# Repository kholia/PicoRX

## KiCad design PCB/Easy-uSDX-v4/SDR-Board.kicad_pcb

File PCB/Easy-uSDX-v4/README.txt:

https://www.w0qe.com/Projects/rf_clipper_2016.html

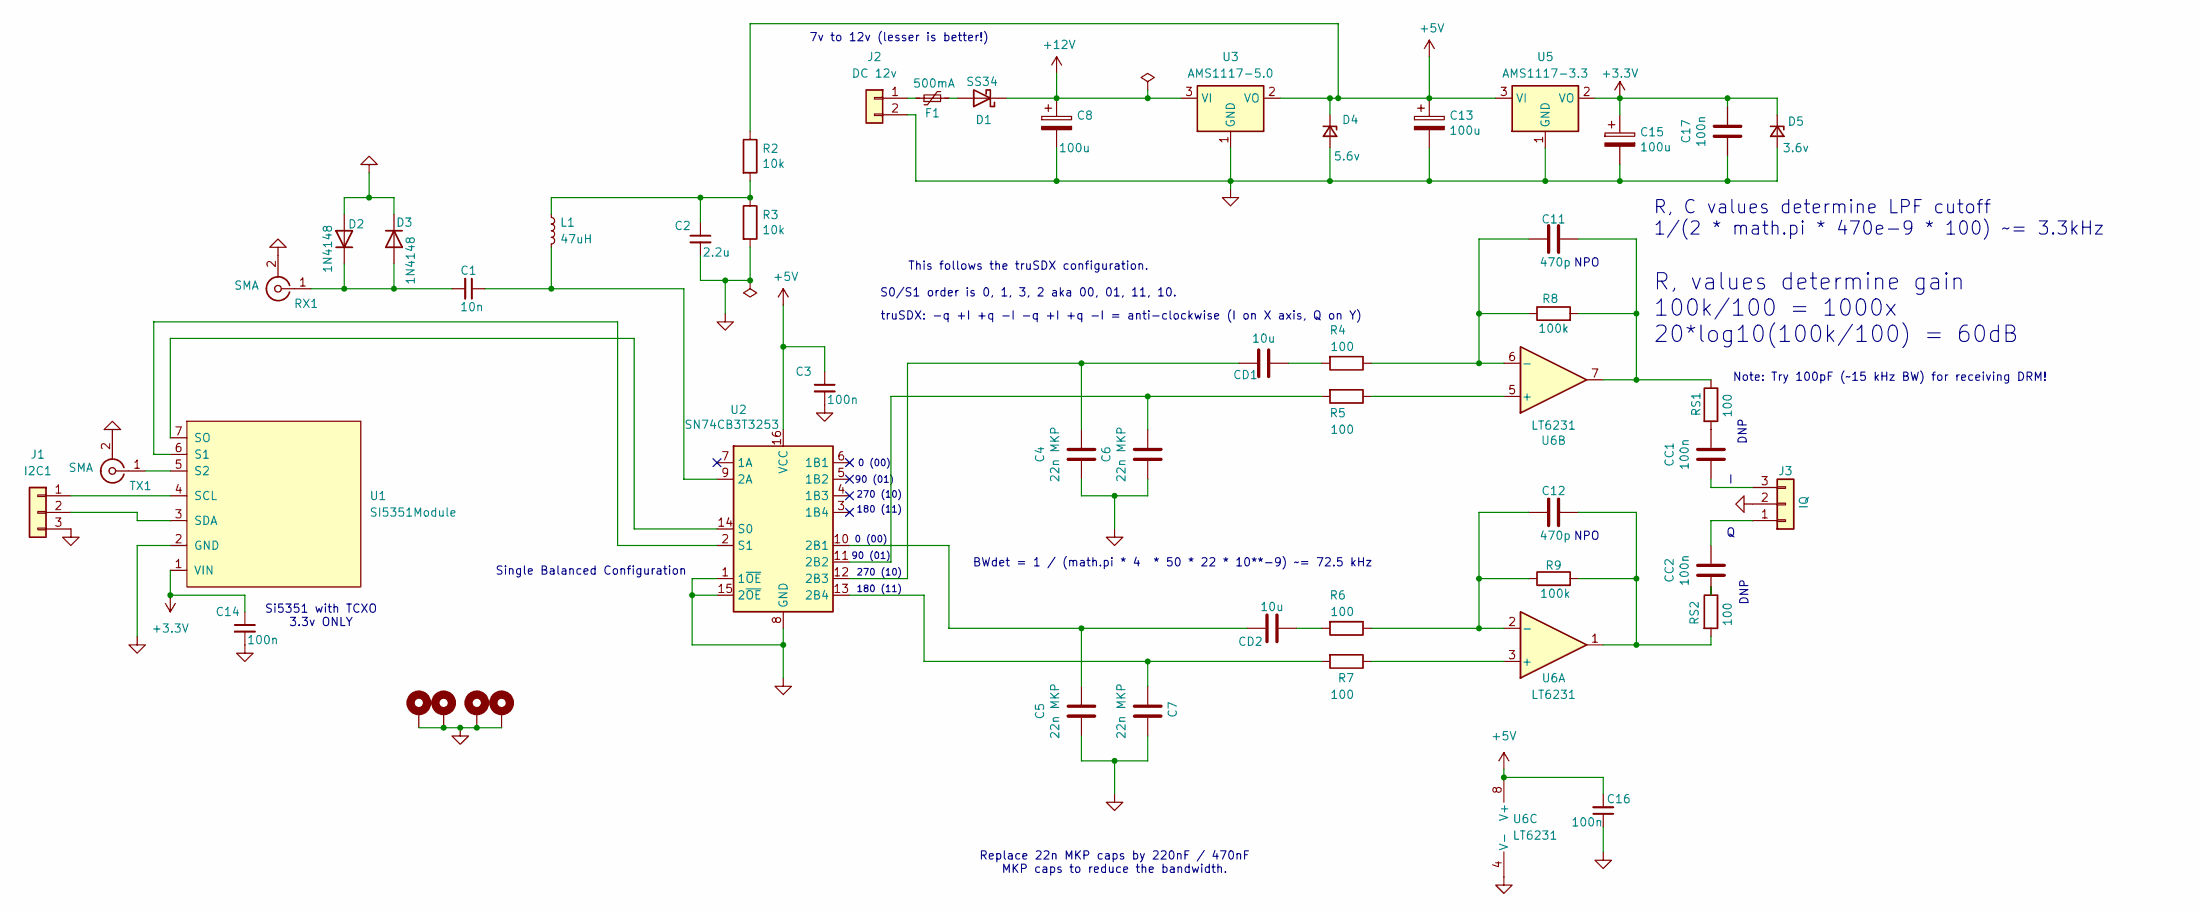
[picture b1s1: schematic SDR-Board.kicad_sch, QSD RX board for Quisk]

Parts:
C1: 10n; C_1206_3216Metric_Pad1.33x1.80mm_HandSolder
C2: 2.2u; C_1206_3216Metric_Pad1.33x1.80mm_HandSolder
C3, C14, C16, C17: 100n; C_1206_3216Metric_Pad1.33x1.80mm_HandSolder
C4, C5, C6, C7: 22n MKP; C_Rect_L7.0mm_W2.0mm_P5.00mm
C8, C13, C15: 100u; CP_Radial_D5.0mm_P2.50mm
C11, C12: 470p; C_1206_3216Metric_Pad1.33x1.80mm_HandSolder
CC1, CC2: 100n; C_1206_3216Metric_Pad1.33x1.80mm_HandSolder
CD1, CD2: 10u; C_1206_3216Metric_Pad1.33x1.80mm_HandSolder
D1: SS34; D_SMA_Handsoldering
D2, D3: 1N4148; D_DO-35_SOD27_P2.54mm_Vertical_KathodeUp
D4: 5.6v; D_SMA
D5: 3.6v; D_SOD-123
F1: 500mA; Fuse_1812_4532Metric_Pad1.30x3.40mm_HandSolder
H1, H2, H3, H4: MountingHole_Pad; MountingHole_3.2mm_M3_Pad_Via
J1: I2C1; PinHeader_1x03_P2.54mm_Vertical
J2: DC 12v; PinHeader_1x02_P2.54mm_Vertical
J3: IQ; PinSocket_1x03_P2.54mm_Vertical
L1: 47uH; L_1210_3225Metric_Pad1.42x2.65mm_HandSolder
R2, R3: 10k; R_1206_3216Metric_Pad1.30x1.75mm_HandSolder
R4, R5, R6, R7: 100; R_1206_3216Metric_Pad1.30x1.75mm_HandSolder
R8, R9: 100k; R_1206_3216Metric_Pad1.30x1.75mm_HandSolder
RS1, RS2: 100; R_1206_3216Metric_Pad1.30x1.75mm_HandSolder
RX1: SMA; SMA_Samtec_SMA-J-P-H-ST-EM1_EdgeMount
TX1: SMA; SMA_Samtec_SMA-J-P-H-ST-EM1_EdgeMount
U1: SI5351Module; SI5351 Module
U2: SN74CB3T3253; SOIC-16_4.55x10.3mm_P1.27mm
U3: AMS1117-5.0; SOT-223-3_TabPin2
U5: AMS1117-3.3; SOT-223-3_TabPin2
U6: LT6231; SO-8_3.9x4.9mm_P1.27mm

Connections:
+3.3V: C14.1, C15.1, C17.2, D5.1 (K), U1.1 (VIN), U5.2 (VO)
+5V: C3.1, C13.1, C16.2, D4.1 (K), R2.1, U2.16 (VCC), U3.2 (VO), U5.3 (VI), U6.8 (V+)
+12V: C8.1, D1.1 (K), U3.3 (VI)
GND: C2.2, C3.2, C4.1, C5.1, C6.1, C7.1, C8.2, C13.2, C14.2, C15.2, C16.1, C17.1, D2.2 (A), D3.1 (K), D4.2 (A), D5.2 (A), H1.1, H2.1, H3.1, H4.1, J1.3, J2.2, J3.2, R3.2, RX1.2 (Ext), TX1.2 (Ext), U1.2 (GND), U2.1 (1~OE), U2.8 (GND), U2.15 (2~OE), U3.1 (GND), U5.1 (GND), U6.4 (V-)
unnamed: C2.1, L1.1, R2.2, R3.1
unnamed: C11.2, R8.2, RS1.1, U6.7
unnamed: C12.2, R9.2, RS2.2, U6.1
unnamed: CC1.2, RS1.2
unnamed: CC2.1, RS2.1
unnamed: CD1.1, R4.2
unnamed: CD2.1, R6.2
unnamed: D1.2 (A), F1.2
unnamed: C1.2, D2.1 (K), D3.2 (A), RX1.1 (In)
unnamed: J1.1, U1.4 (SCL)
unnamed: J1.2, U1.3 (SDA)
unnamed: F1.1, J2.1
unnamed: CC2.2, J3.1
unnamed: CC1.1, J3.3
unnamed: TX1.1 (In), U1.5 (S2)
unnamed: U1.6 (S1), U2.2 (S1)
unnamed: U1.7 (SO), U2.14 (S0)
unnamed: C1.1, L1.2, U2.9 (2A)
unnamed: C5.2, CD2.2, U2.10 (2B1)
unnamed: C6.2, R5.2, U2.11 (2B2)
unnamed: C4.2, CD1.2, U2.12 (2B3)
unnamed: C7.2, R7.2, U2.13 (2B4)
unnamed: R7.1, U6.3 (+)
unnamed: C12.1, R6.1, R9.1, U6.2 (-)
unnamed: R5.1, U6.5 (+)
unnamed: C11.1, R4.1, R8.1, U6.6 (-)

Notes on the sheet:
truSDX: -q +I +q -I -q +I +q -I = anti-clockwise (I on X axis, Q on Y)
NPO
7v to 12v (lesser is better!)
DNP
0 (00)
180 (11)
BWdet = 1 / (math.pi * 4 * 50 * 22 * 10**-9) ~= 72.5 kHz
R, values determine gain 100k/100 = 1000x 20*log10(100k/100) = 60dB
Note: Try 100pF (~15 kHz BW) for receiving DRM!
Replace 22n MKP caps by 220nF / 470nF MKP caps to reduce the bandwidth.
90 (01)
270 (10)
R, C values determine LPF cutoff 1/(2 * math.pi * 470e-9 * 100) ~= 3.3kHz
Si5351 with TCXO 3.3v ONLY
Single Balanced Configuration
This follows the truSDX configuration. S0/S1 order is 0, 1, 3, 2 aka 00, 01, 11, 10.

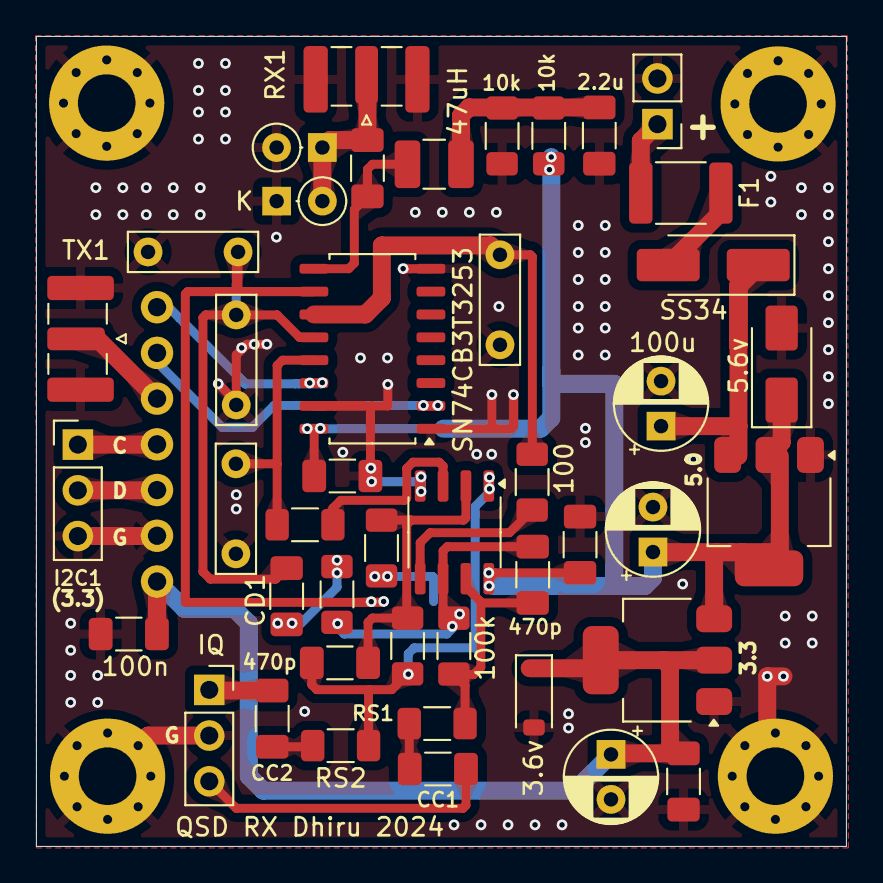
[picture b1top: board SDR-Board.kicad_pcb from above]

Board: 2 copper layers, 45.0 x 45.0 mm, 50 parts (1 on the bottom side), 30 nets.

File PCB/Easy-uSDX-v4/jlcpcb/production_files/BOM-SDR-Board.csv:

Comment,Designator,Footprint,LCSC
470p,"C11,C12",C_1206_3216Metric_Pad1.33x1.80mm_HandSolder,C107177
100k,"R8,R9",R_1206_3216Metric_Pad1.30x1.75mm_HandSolder,C17900
100,"R4,R5,R6,R7,RS1,RS2",R_1206_3216Metric_Pad1.30x1.75mm_HandSolder,C17901
10k,"R2,R3",R_1206_3216Metric_Pad1.30x1.75mm_HandSolder,C17902
10n,C1,C_1206_3216Metric_Pad1.33x1.80mm_HandSolder,C1846
5.6v,D4,D_SMA,C20555
100n,"C14,C16,C17,C3,CC1,CC2",C_1206_3216Metric_Pad1.33x1.80mm_HandSolder,C24497
SN74CB3T3253,U2,SOIC-16_4.55x10.3mm_P1.27mm,C2674609
47uH,L1,L_1210_3225Metric_Pad1.42x2.65mm_HandSolder,C361668
2.2u,C2,C_1206_3216Metric_Pad1.33x1.80mm_HandSolder,C50254
LT6231,U6,SO-8_3.9x4.9mm_P1.27mm,C580237
AMS1117-3.3,U5,SOT-223-3_TabPin2,C6186
AMS1117-5.0,U3,SOT-223-3_TabPin2,C6187
SS34,D1,D_SMA_Handsoldering,C8678
22n MKP,C5,C_Rect_L7.0mm_W2.0mm_P5.00mm,
MountingHole_Pad,H4,MountingHole_3.2mm_M3_Pad_Via,
IQ,J3,PinSocket_1x03_P2.54mm_Vertical,
SI5351Module,U1,SI5351 Module,
22n MKP,C7,C_Rect_L7.0mm_W2.0mm_P5.00mm,
SMA,RX1,SMA_Samtec_SMA-J-P-H-ST-EM1_EdgeMount,
1N4148,D3,D_DO-35_SOD27_P2.54mm_Vertical_KathodeUp,
100u,C8,CP_Radial_D5.0mm_P2.50mm,
MountingHole_Pad,H2,MountingHole_3.2mm_M3_Pad_Via,
100u,C15,CP_Radial_D5.0mm_P2.50mm,
I2C1,J1,PinHeader_1x03_P2.54mm_Vertical,
22n MKP,C6,C_Rect_L7.0mm_W2.0mm_P5.00mm,
SMA,TX1,SMA_Samtec_SMA-J-P-H-ST-EM1_EdgeMount,
MountingHole_Pad,H1,MountingHole_3.2mm_M3_Pad_Via,
1N4148,D2,D_DO-35_SOD27_P2.54mm_Vertical_KathodeUp,
100u,C13,CP_Radial_D5.0mm_P2.50mm,
DC 12v,J2,PinHeader_1x02_P2.54mm_Vertical,
MountingHole_Pad,H3,MountingHole_3.2mm_M3_Pad_Via,
22n MKP,C4,C_Rect_L7.0mm_W2.0mm_P5.00mm,
500mA,F1,Fuse_1812_4532Metric_Pad1.30x3.40mm_HandSolder,
3.6v,D5,D_SOD-123,
10u,CD1,C_1206_3216Metric_Pad1.33x1.80mm_HandSolder,
10u,CD2,C_1206_3216Metric_Pad1.33x1.80mm_HandSolder,

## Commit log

2024-06-25 Easy-uSDX-v4
